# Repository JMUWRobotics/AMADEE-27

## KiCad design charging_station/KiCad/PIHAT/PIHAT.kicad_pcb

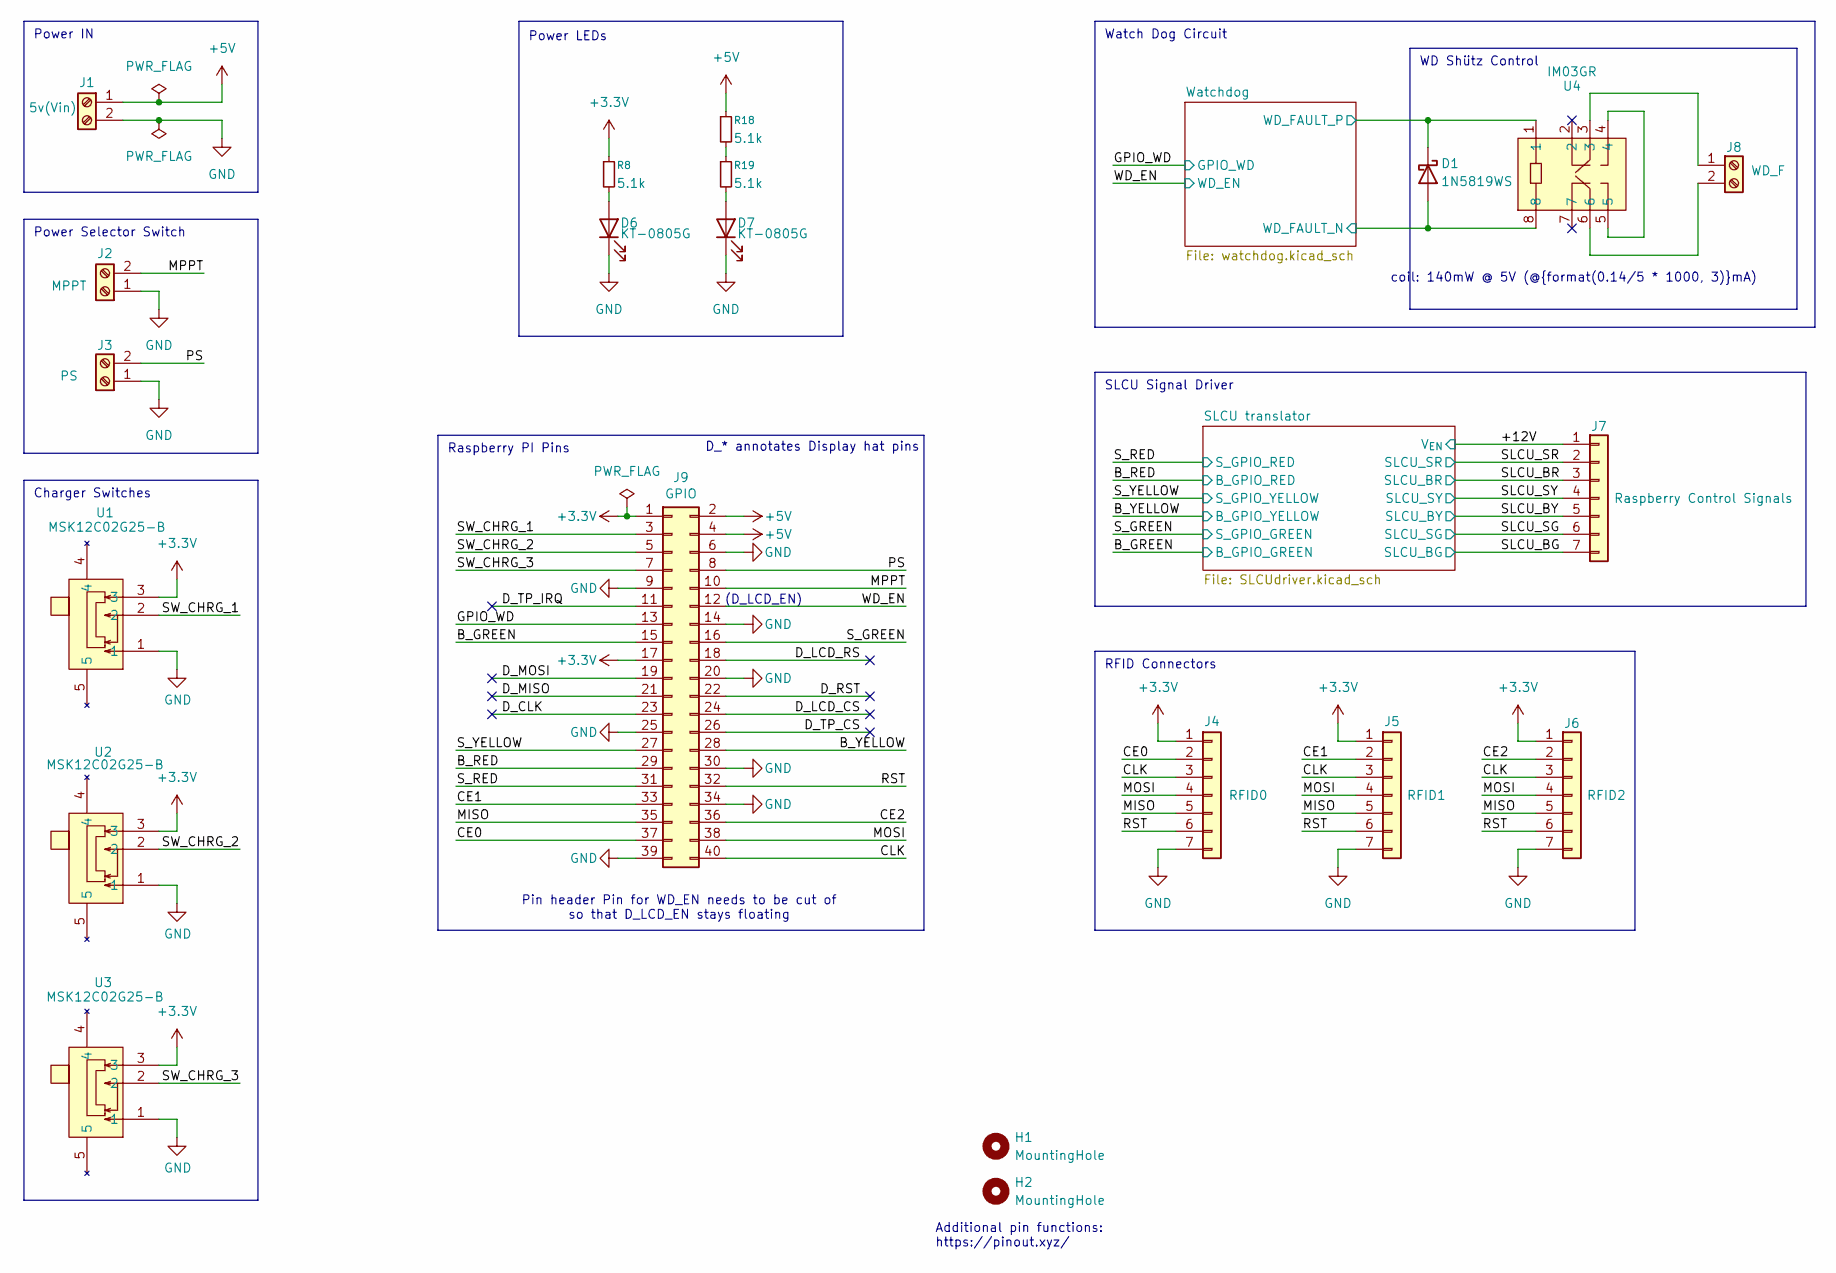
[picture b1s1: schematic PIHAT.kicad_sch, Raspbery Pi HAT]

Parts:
D1: 1N5819WS; D_SOD-323; LCSC C191023
D6, D7: KT-0805G; LED_0805_2012Metric; MPN KT-0805G; LCSC Part C2297
H1: MountingHole; MountingHole_2.2mm_M2_DIN965_Pad
H2: MountingHole; MountingHole_2.5mm_Pad
J1: 5v(Vin); TerminalBlock_Phoenix_PT-1,5-2-5.0-H_1x02_P5.00mm_Horizontal; MPN 1935161; LCSC Part C3819953
J2: MPPT; TerminalBlock_Phoenix_PT-1,5-2-5.0-H_1x02_P5.00mm_Horizontal; MPN 1935161; LCSC Part C3819953
J3: PS; TerminalBlock_Phoenix_PT-1,5-2-5.0-H_1x02_P5.00mm_Horizontal; MPN 1935161; LCSC Part C3819953
J4: RFID0; JST_XH_S7B-XH-A_1x07_P2.50mm_Horizontal; MPN S7B-XH-A(LF)(SN); LCSC Part C157916
J5: RFID1; JST_XH_S7B-XH-A_1x07_P2.50mm_Horizontal; MPN S7B-XH-A(LF)(SN); LCSC Part C157916
J6: RFID2; JST_XH_S7B-XH-A_1x07_P2.50mm_Horizontal; MPN S7B-XH-A(LF)(SN); LCSC Part C157916
J7: Raspberry Control Signals; JST_XH_S7B-XH-A_1x07_P2.50mm_Horizontal; MPN S7B-XH-A(LF)(SN); LCSC Part C157916
J8: WD_F; TerminalBlock_Phoenix_PT-1,5-2-5.0-H_1x02_P5.00mm_Horizontal; MPN 1935161; LCSC Part C3819953
J9: GPIO; PinSocket_2x20_P2.54mm_Vertical; MPN SSQ-120-03-T-D; LCSC C6235776
R8, R18, R19: 5.1k; R_0603_1608Metric; LCSC C17414
U1, U2, U3: MSK12C02G25-B; SW-SMD_MSK12C02G25-B; MPN MSK12C02G25-B; LCSC Part C22435663
U4: IM03GR; RELAY-SMD_IMXXGR; MPN IM03GR; LCSC Part C2153100

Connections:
+3.3V: J4.1, J5.1, J6.1, J9.1, J9.17, R8.1, U1.3, U2.3, U3.3; also elsewhere on the board
+5V: J1.1, J9.2, J9.4, R18.1; also elsewhere on the board
/+12V: J7.1; also elsewhere on the board
/B_GREEN: J9.15; also elsewhere on the board
/B_RED: J9.29; also elsewhere on the board
/B_YELLOW: J9.28; also elsewhere on the board
/CE0: J4.2, J9.37
/CE1: J5.2, J9.33
/CE2: J6.2, J9.36
/CLK: J4.3, J5.3, J6.3, J9.40
/D_CLK: J9.23
/D_LCD_CS: J9.24
/D_LCD_RS: J9.18
/D_MISO: J9.21
/D_MOSI: J9.19
/D_RST: J9.22
/D_TP_CS: J9.26
/D_TP_IRQ: J9.11
/GPIO_WD: J9.13; also elsewhere on the board
/MISO: J4.5, J5.5, J6.5, J9.35
/MOSI: J4.4, J5.4, J6.4, J9.38
/MPPT: J2.2, J9.10
/PS: J3.2, J9.8
/RST: J4.6, J5.6, J6.6, J9.32
/SLCU_BG: J7.7; also elsewhere on the board
/SLCU_BR: J7.3; also elsewhere on the board
/SLCU_BY: J7.5; also elsewhere on the board
/SLCU_SG: J7.6; also elsewhere on the board
/SLCU_SR: J7.2; also elsewhere on the board
/SLCU_SY: J7.4; also elsewhere on the board
/SW_CHRG_1: J9.3, U1.2
/SW_CHRG_2: J9.5, U2.2
/SW_CHRG_3: J9.7, U3.2
/S_GREEN: J9.16; also elsewhere on the board
/S_RED: J9.31; also elsewhere on the board
/S_YELLOW: J9.27; also elsewhere on the board
/WD_EN: J9.12; also elsewhere on the board
/Watchdog/WD_FAULT_N: D1.2 (A), U4.8; also elsewhere on the board
/Watchdog/WD_FAULT_P: D1.1 (K), U4.1; also elsewhere on the board
GND: D6.1 (K), D7.1 (K), J1.2, J2.1, J3.1, J4.7, J5.7, J6.7, J9.6, J9.9, J9.14, J9.20, J9.25, J9.30, J9.34, J9.39, U1.1, U2.1, U3.1; also elsewhere on the board
unnamed: D6.2 (A), R8.2
unnamed: D7.2 (A), R19.2
unnamed: J8.1, U4.3
unnamed: J8.2, U4.6
unnamed: R18.2, R19.1
unnamed: U4.4, U4.5

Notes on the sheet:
Raspberry PI Pins
(D_LCD_EN)
Additional pin functions: https://pinout.xyz/
SLCU Signal Driver
RFID Connectors
WD Shütz Control
Pin header Pin for WD_EN needs to be cut of so that D_LCD_EN stays floating
Power Selector Switch
Watch Dog Circuit
Power LEDs
Charger Switches
Power IN
coil: 140mW @ 5V (@{format(0.14/5 * 1000, 3)}mA)
D_* annotates Display hat pins

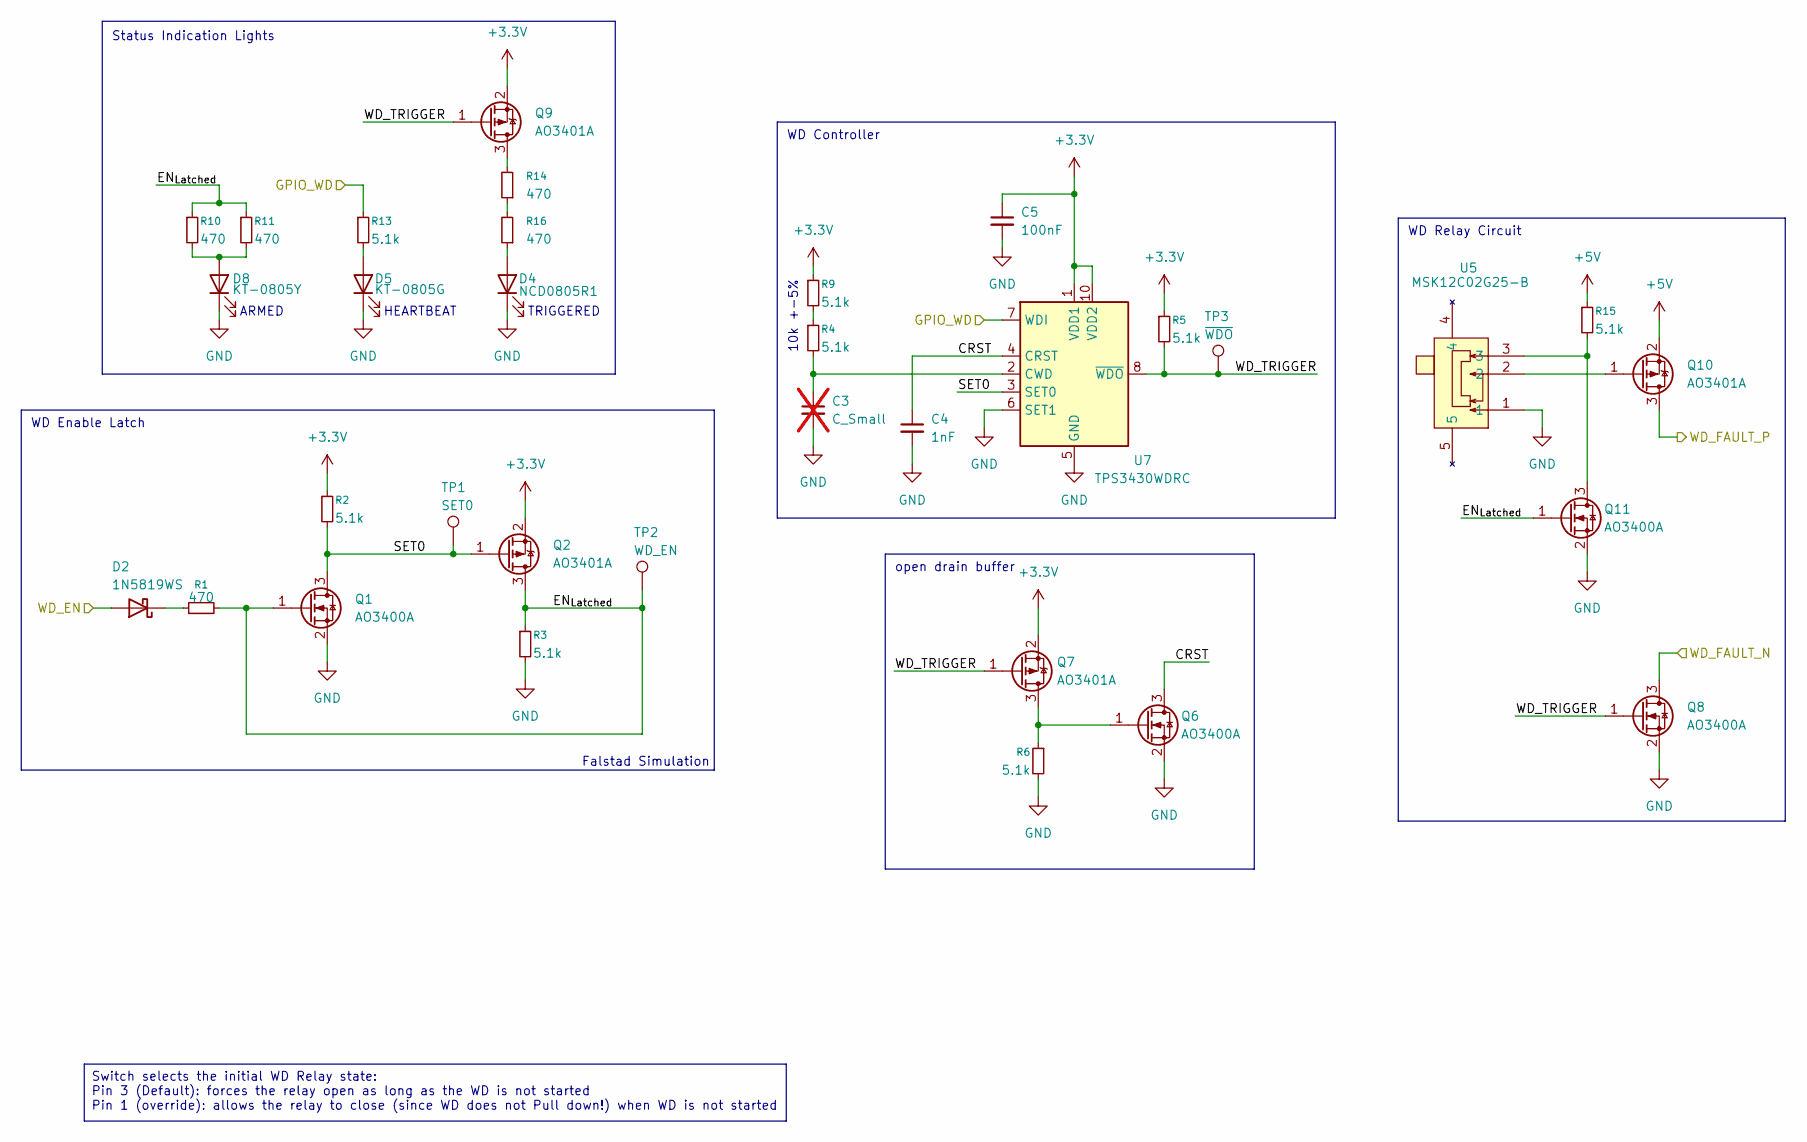
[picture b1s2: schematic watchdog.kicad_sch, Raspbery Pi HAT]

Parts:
C3: C_Small; C_0805_2012Metric_Pad1.18x1.45mm_HandSolder; not fitted
C4: 1nF; C_0603_1608Metric
C5: 100nF; C_0603_1608Metric; LCSC Part C14663
D2: 1N5819WS; D_SOD-323; LCSC C191023
D4: NCD0805R1; LED_0805_2012Metric; MPN NCD0805R1; LCSC Part C84256
D5: KT-0805G; LED_0805_2012Metric; MPN KT-0805G; LCSC Part C2297
D8: KT-0805Y; LED_0805_2012Metric; MPN KT-0805Y; LCSC Part C2296
Q1, Q6, Q8, Q11: AO3400A; SOT-23; MPN AO3400A; LCSC Part C15127
Q2, Q7, Q9, Q10: AO3401A; SOT-23; MPN AO3401A; LCSC Part C15127
R1, R10, R11, R14, R16: 470; R_0603_1608Metric; LCSC C23179
R2, R3, R4, R5, R6, R9, R13, R15: 5.1k; R_0603_1608Metric; LCSC C17414
TP1: SET0; TestPoint_Pad_D1.0mm
TP2: WD_EN; TestPoint_Pad_D1.0mm
TP3: ~{WDO}; TestPoint_Pad_D1.0mm
U5: MSK12C02G25-B; SW-SMD_MSK12C02G25-B; MPN MSK12C02G25-B; LCSC Part C22435663
U7: TPS3430WDRC; VSON-10-1EP_3x3mm_P0.5mm_EP1.65x2.4mm

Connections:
+3.3V: C5.1, Q2.2 (S), Q7.2 (S), Q9.2 (S), R2.1, R5.1, R9.1, U7.1 (VDD1), U7.10 (VDD2); also elsewhere on the board
+5V: Q10.2 (S), R15.1; also elsewhere on the board
/GPIO_WD: R13.1, U7.7 (WDI); also elsewhere on the board
/WD_EN: D2.2 (A); also elsewhere on the board
/Watchdog/CRST: C4.1, Q6.3 (D), U7.4 (CRST)
/Watchdog/EN_{Latched}: Q1.1 (G), Q2.3 (D), Q11.1 (G), R1.2, R3.1, R10.1, R11.1, TP2.1 (1_1)
/Watchdog/SET0: Q1.3 (D), Q2.1 (G), R2.2, TP1.1 (1_1), U7.3 (SET0)
/Watchdog/WD_FAULT_N: Q8.3 (D); also elsewhere on the board
/Watchdog/WD_FAULT_P: Q10.3 (D); also elsewhere on the board
/Watchdog/WD_TRIGGER: Q7.1 (G), Q8.1 (G), Q9.1 (G), R5.2, TP3.1 (1_1), U7.8 (~WDO)
GND: C3.2, C4.2, C5.2, D4.1 (K), D5.1 (K), D8.1 (K), Q1.2 (S), Q6.2 (S), Q8.2 (S), Q11.2 (S), R3.2, R6.2, U5.1, U7.5 (GND), U7.6 (SET1), U7.11 (GND); also elsewhere on the board
unnamed: D2.1 (K), R1.1
unnamed: D4.2 (A), R16.1
unnamed: D5.2 (A), R13.2
unnamed: D8.2 (A), R10.2, R11.2
unnamed: Q6.1 (G), Q7.3 (D), R6.1
unnamed: Q9.3 (D), R14.2
unnamed: Q10.1 (G), U5.2
unnamed: Q11.3 (D), R15.2, U5.3
unnamed: R4.1, R9.2
unnamed: R14.1, R16.2
unnamed: C3.1, R4.2, U7.2 (CWD)

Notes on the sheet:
HEARTBEAT
open drain buffer
10k +-5%
Falstad Simulation
WD Enable Latch
TRIGGERED
Status Indication Lights
ARMED
WD Controller
WD Relay Circuit
Switch selects the initial WD Relay state: Pin 3 (Default): forces the relay open as long as the WD is not started Pin 1 (override): allows the relay to close (since WD does not Pull down!) when WD is not started

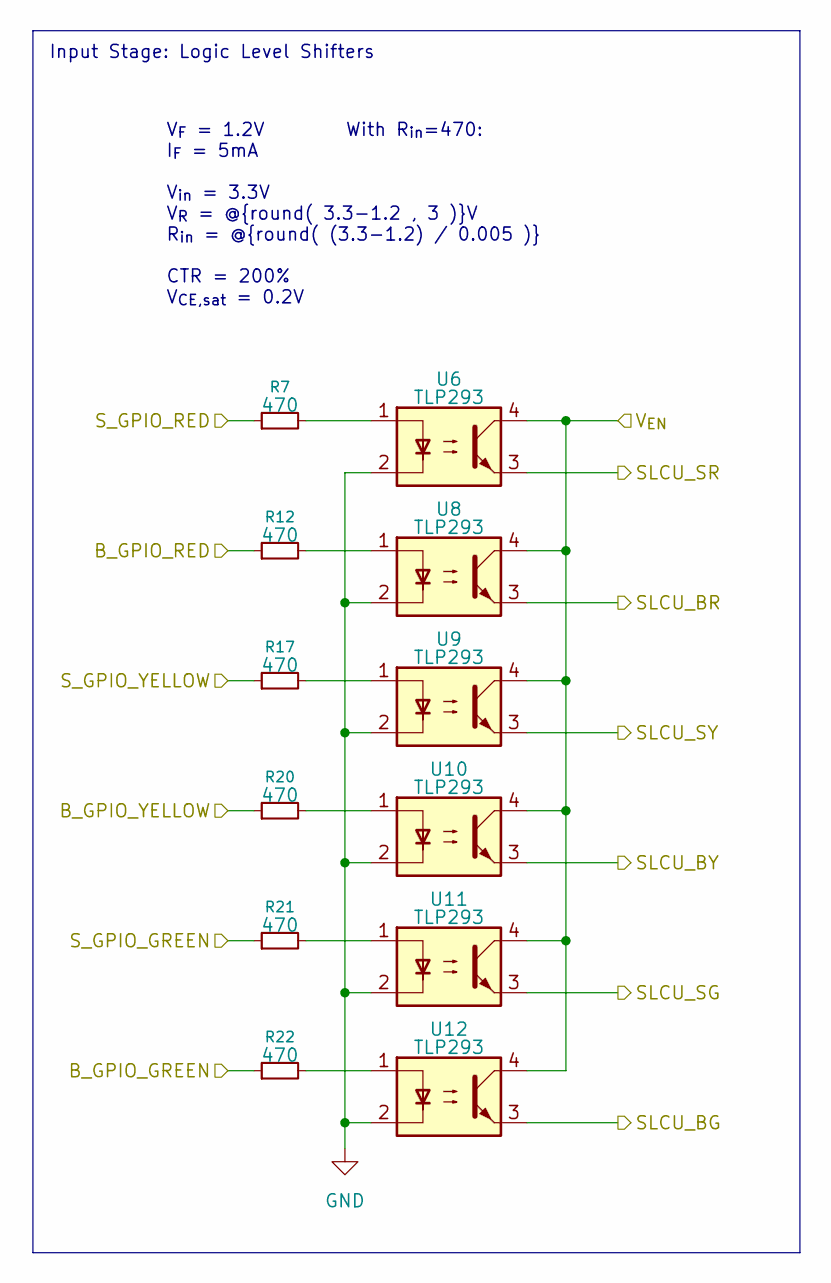
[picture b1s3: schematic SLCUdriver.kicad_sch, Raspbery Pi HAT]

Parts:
R7, R12, R17, R20, R21, R22: 470; R_0603_1608Metric; LCSC C23179
U6, U8, U9, U10, U11, U12: TLP293; SOIC-4_4.55x2.6mm_P1.27mm; MPN TLP293(BLL-TPL,E; LCSC C3008594

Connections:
/+12V: U6.4, U8.4, U9.4, U10.4, U11.4, U12.4; also elsewhere on the board
/B_GREEN: R22.1; also elsewhere on the board
/B_RED: R12.1; also elsewhere on the board
/B_YELLOW: R20.1; also elsewhere on the board
/SLCU_BG: U12.3; also elsewhere on the board
/SLCU_BR: U8.3; also elsewhere on the board
/SLCU_BY: U10.3; also elsewhere on the board
/SLCU_SG: U11.3; also elsewhere on the board
/SLCU_SR: U6.3; also elsewhere on the board
/SLCU_SY: U9.3; also elsewhere on the board
/S_GREEN: R21.1; also elsewhere on the board
/S_RED: R7.1; also elsewhere on the board
/S_YELLOW: R17.1; also elsewhere on the board
GND: U6.2, U8.2, U9.2, U10.2, U11.2, U12.2; also elsewhere on the board
unnamed: R7.2, U6.1
unnamed: R12.2, U8.1
unnamed: R17.2, U9.1
unnamed: R20.2, U10.1
unnamed: R21.2, U11.1
unnamed: R22.2, U12.1

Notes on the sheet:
With R_{in}=470:
V_{F} = 1.2V I_{F} = 5mA V_{in} = 3.3V V_{R} = @{round( 3.3-1.2 , 3 )}V R_{in} = @{round( (3.3-1.2) / 0.005 )} CTR = 200% V_{CE,sat} = 0.2V
Input Stage: Logic Level Shifters

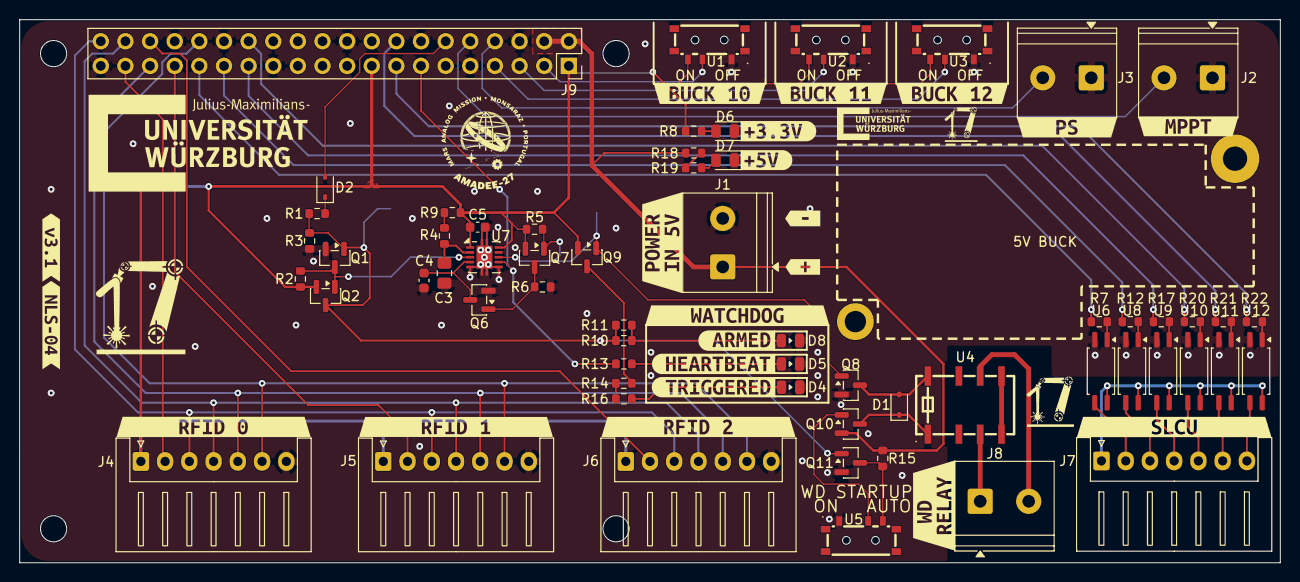
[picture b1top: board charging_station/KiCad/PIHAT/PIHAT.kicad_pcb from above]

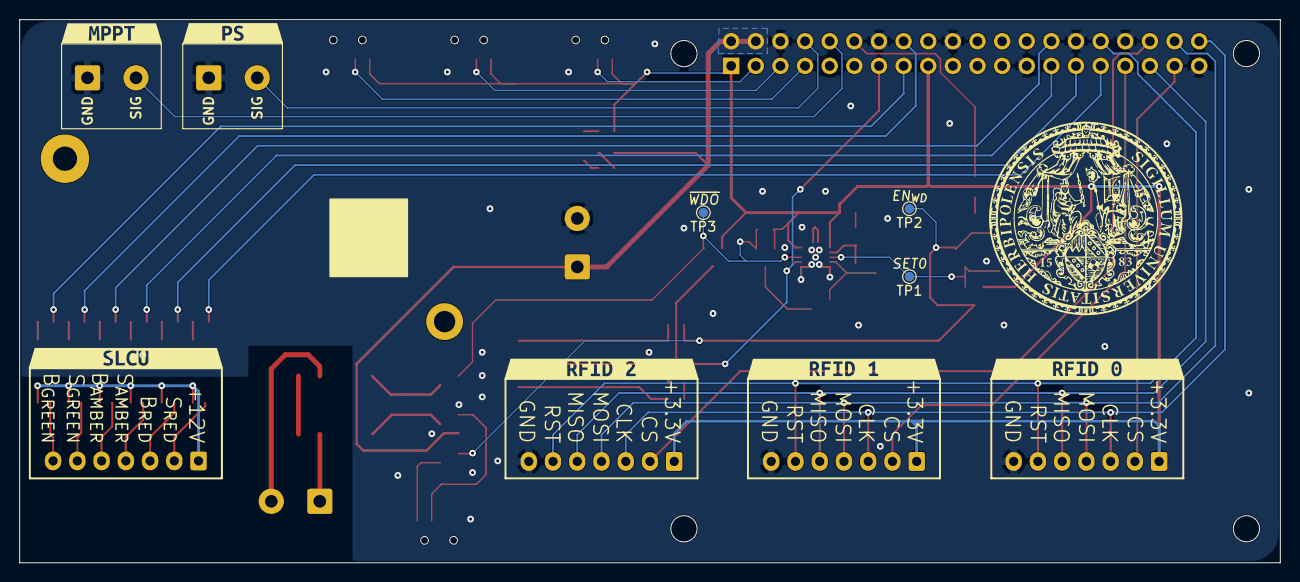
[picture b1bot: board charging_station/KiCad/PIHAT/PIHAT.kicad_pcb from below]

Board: 2 copper layers, 130.0 x 56.0 mm, 97 parts (13 on the bottom side), 59 nets.

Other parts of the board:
MH1, MH2, MH3, MH4: MountingHole_2.7mm_M2.5
kibuzzard-6AD53C3D: G***; kibuzzard-6AD53C3D
kibuzzard-6AD53C20, kibuzzard-6AD53C20#2: G***; kibuzzard-6AD53C20
kibuzzard-6AD53C43: G***; kibuzzard-6AD53C43
kibuzzard-6AD53C84: G***; kibuzzard-6AD53C84
kibuzzard-6AD53CF1: G***; kibuzzard-6AD53CF1
kibuzzard-6AD53D49: G***; kibuzzard-6AD53D49
kibuzzard-6AD53DF3: G***; kibuzzard-6AD53DF3
kibuzzard-6AD53E3A: G***; kibuzzard-6AD53E3A
kibuzzard-6AD53E40: G***; kibuzzard-6AD53E40
kibuzzard-6AD530C8: G***; kibuzzard-6AD530C8
kibuzzard-6AD530EA: G***; kibuzzard-6AD530EA
kibuzzard-6AD537E7: G***; kibuzzard-6AD537E7
kibuzzard-6AD540AE: G***; kibuzzard-6AD540AE
kibuzzard-6AD541D1: G***; kibuzzard-6AD541D1
kibuzzard-6AD543B1: G***; kibuzzard-6AD543B1
kibuzzard-6AD543B7: G***; kibuzzard-6AD543B7
kibuzzard-6AD554A5: G***; kibuzzard-6AD554A5
kibuzzard-6AD5310E: G***; kibuzzard-6AD5310E
kibuzzard-6AD5403C: G***; kibuzzard-6AD5403C
kibuzzard-6AD54089: G***; kibuzzard-6AD54089
kibuzzard-6AF5E61E: G***; kibuzzard-6AF5E61E
kibuzzard-6AF5E623: G***; kibuzzard-6AF5E623
kibuzzard-6AF5EA3F: G***; kibuzzard-6AF5EA3F
kibuzzard-6AF5F1CD: G***; kibuzzard-6AF5F1CD
kibuzzard-6AF5F1D2: G***; kibuzzard-6AF5F1D2
kibuzzard-6AF35593: G***; kibuzzard-6AF35593

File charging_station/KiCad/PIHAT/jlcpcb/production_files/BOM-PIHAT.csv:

Comment,Designator,Footprint,LCSC,Quantity
100nF,C5,C_0603_1608Metric,C14663,1
1N5819WS,"D1,D2",D_SOD-323,C191023,2
1nF,C4,C_0603_1608Metric,C1588,1
470,"R1,R10,R11,R12,R14,R16,R17,R20,R21,R22,R7",R_0603_1608Metric,C23179,11
5.1k,"R13,R15,R18,R19,R2,R3,R4,R5,R6,R8,R9",R_0603_1608Metric,C23186,11
5v(Vin),J1,"TerminalBlock_Phoenix_PT-1,5-2-5.0-H_1x02_P5.00mm_Horizontal",C3819953,1
AO3400A,"Q1,Q11,Q6,Q8",SOT-23,C20917,4
AO3401A,"Q10,Q2,Q7,Q9",SOT-23,C15127,4
GPIO,J9,PinSocket_2x20_P2.54mm_Vertical,C6235776,1
IM03GR,U4,RELAY-SMD_IMXXGR,C2153100,1
KT-0805G,"D5,D6,D7",LED_0805_2012Metric,C2297,3
KT-0805Y,D8,LED_0805_2012Metric,C2296,1
MPPT,J2,"TerminalBlock_Phoenix_PT-1,5-2-5.0-H_1x02_P5.00mm_Horizontal",C3819953,1
MSK12C02G25-B,"U1,U2,U3,U5",SW-SMD_MSK12C02G25-B,C22435663,4
NCD0805R1,D4,LED_0805_2012Metric,C84256,1
PS,J3,"TerminalBlock_Phoenix_PT-1,5-2-5.0-H_1x02_P5.00mm_Horizontal",C3819953,1
RFID0,J4,JST_XH_S7B-XH-A_1x07_P2.50mm_Horizontal,C157916,1
RFID1,J5,JST_XH_S7B-XH-A_1x07_P2.50mm_Horizontal,C157916,1
RFID2,J6,JST_XH_S7B-XH-A_1x07_P2.50mm_Horizontal,C157916,1
Raspberry Control Signals,J7,JST_XH_S7B-XH-A_1x07_P2.50mm_Horizontal,C157916,1
TLP293,"U10,U11,U12,U6,U8,U9",SOIC-4_4.55x2.6mm_P1.27mm,C3008594,6
TPS3430WDRC,U7,VSON-10-1EP_3x3mm_P0.5mm_EP1.65x2.4mm,C2870545,1
WD_F,J8,"TerminalBlock_Phoenix_PT-1,5-2-5.0-H_1x02_P5.00mm_Horizontal",C3819953,1

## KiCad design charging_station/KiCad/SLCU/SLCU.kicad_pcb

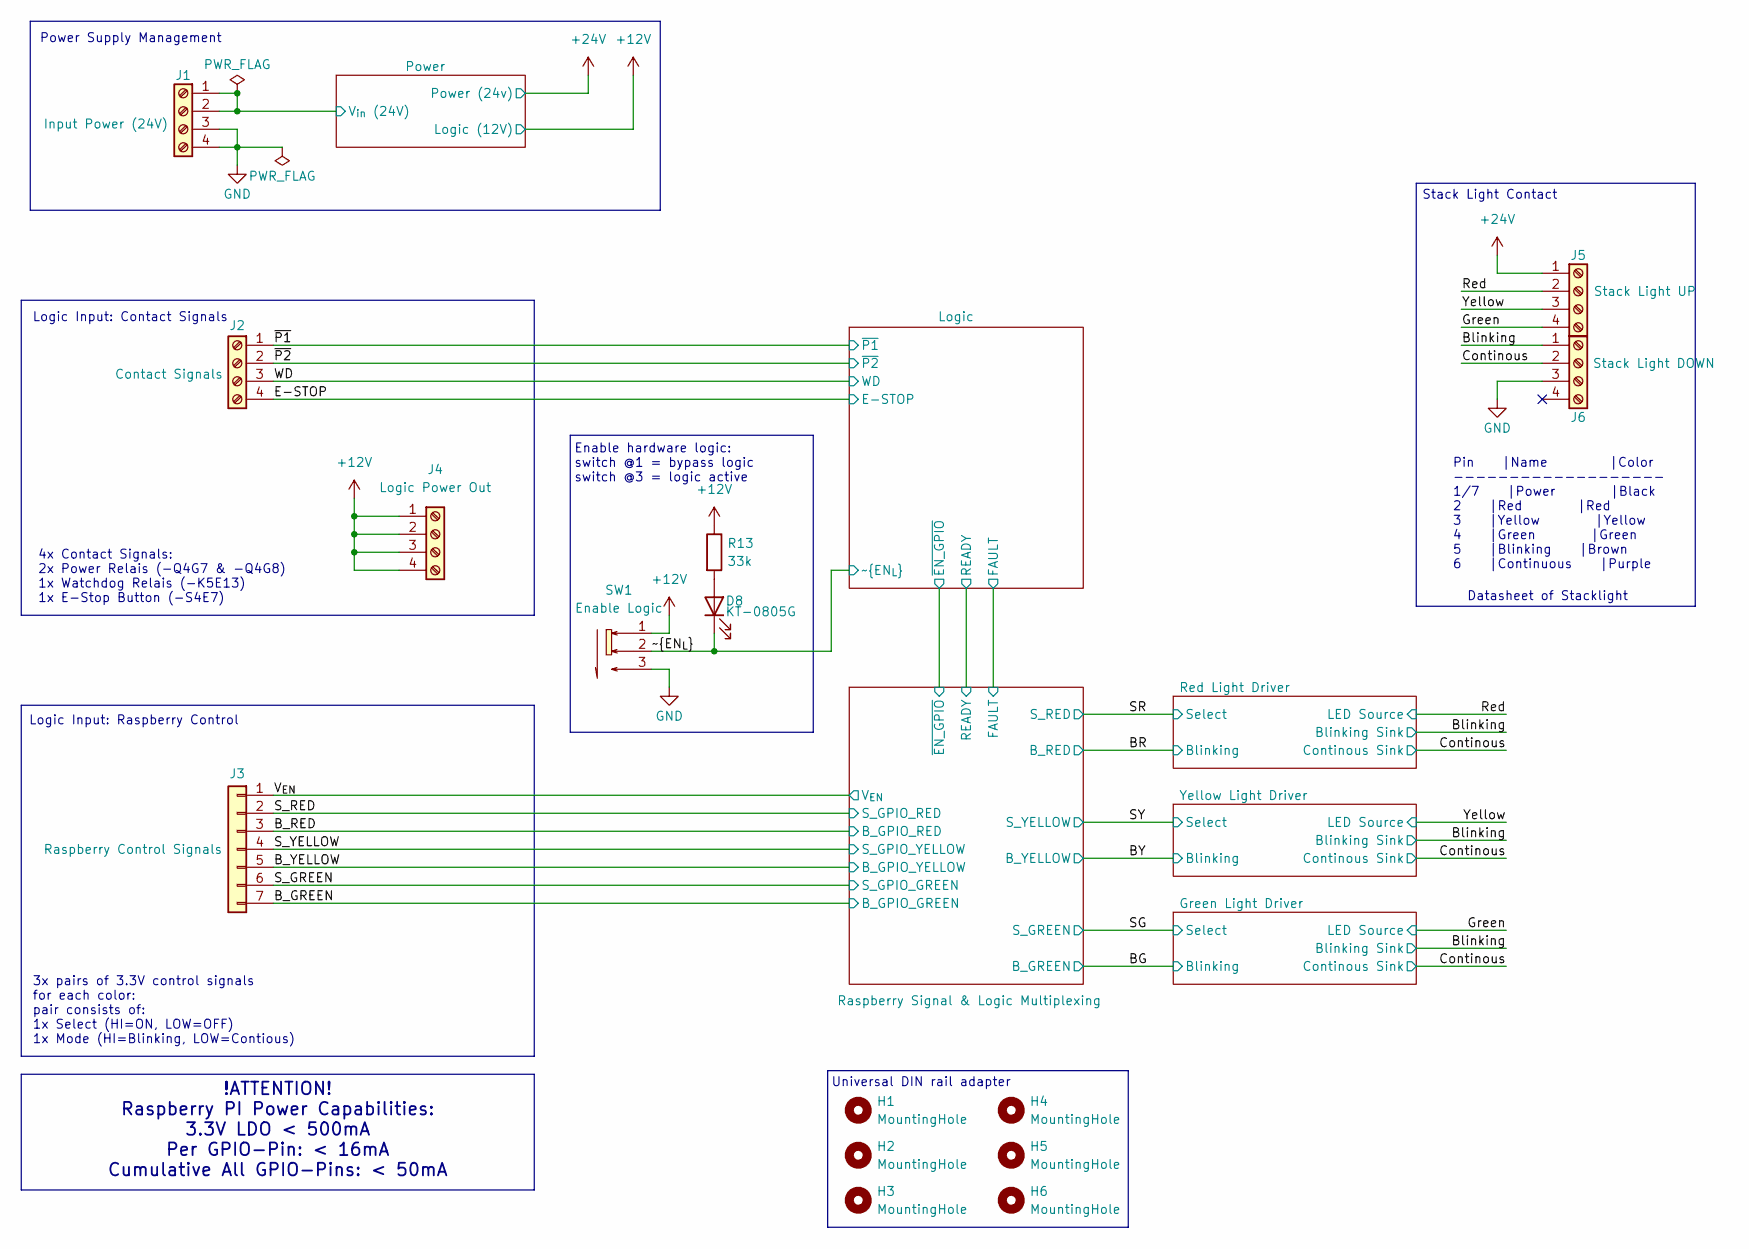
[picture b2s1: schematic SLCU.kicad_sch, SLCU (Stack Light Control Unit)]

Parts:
D8: KT-0805G; LED_0805_2012Metric_Pad1.15x1.40mm_HandSolder; MPN KT-0805G; LCSC Part C2297
H1, H2, H3, H4, H5, H6: MountingHole; MountingHole_3.2mm_M3
J1: Input Power (24V); TerminalBlock_Phoenix_MKDS-1,5-4_1x04_P5.00mm_Horizontal; MPN 1935187; LCSC Part C3817931
J2: Contact Signals; TerminalBlock_Phoenix_MKDS-1,5-4_1x04_P5.00mm_Horizontal; MPN 1935187; LCSC Part C3817931
J3: Raspberry Control Signals; JST_XH_S7B-XH-A_1x07_P2.50mm_Horizontal; MPN S7B-XH-A(LF)(SN); LCSC Part C157916
J4: Logic Power Out; TerminalBlock_Phoenix_MKDS-1,5-4_1x04_P5.00mm_Horizontal; MPN 1935187; LCSC Part C3817931
J5: Stack Light UP; TerminalBlock_Phoenix_MKDS-1,5-4_1x04_P5.00mm_Horizontal; MPN 1935187; LCSC Part C3817931
J6: Stack Light DOWN; TerminalBlock_Phoenix_MKDS-1,5-4_1x04_P5.00mm_Horizontal; MPN 1935187; LCSC Part C3817931
R13: 33k; R_0402_1005Metric; LCSC Part C25779
SW1: Enable Logic; SW-SMD_SHOUHAN_MST-22D18G23J_C2875122; MPN MST-22D18G2 3J; LCSC Part C2875122

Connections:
+12V: J4.1, J4.2, J4.3, J4.4, R13.1, SW1.1; also elsewhere on the board
+24V: J5.1; also elsewhere on the board
/B_GREEN: J3.7; also elsewhere on the board
/B_RED: J3.3; also elsewhere on the board
/B_YELLOW: J3.5; also elsewhere on the board
/Blinking: J6.1; also elsewhere on the board
/Continous: J6.2; also elsewhere on the board
/E-STOP: J2.4; also elsewhere on the board
/Green: J5.4; also elsewhere on the board
/Power/V_{in} (24V): J1.1, J1.2; also elsewhere on the board
/Red: J5.2; also elsewhere on the board
/S_GREEN: J3.6; also elsewhere on the board
/S_RED: J3.2; also elsewhere on the board
/S_YELLOW: J3.4; also elsewhere on the board
/V_{EN}: J3.1; also elsewhere on the board
/WD: J2.3; also elsewhere on the board
/Yellow: J5.3; also elsewhere on the board
/~EN_{L}: D8.1 (K), SW1.2; also elsewhere on the board
/~P1: J2.1; also elsewhere on the board
/~P2: J2.2; also elsewhere on the board
GND: J1.3, J1.4, J6.3, SW1.3; also elsewhere on the board
unnamed: D8.2 (A), R13.2

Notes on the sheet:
Enable hardware logic: switch @1 = bypass logic switch @3 = logic active
Logic Input: Raspberry Control
Power Supply Management
Datasheet of Stacklight
Pin |Name |Color ------------------- 1/7 |Power |Black 2 |Red |Red 3 |Yellow |Yellow 4 |Green |Green 5 |Blinking |Brown 6 |Continuous |Purple
Logic Input: Contact Signals
3x pairs of 3.3V control signals for each color: pair consists of: 1x Select (HI=ON, LOW=OFF) 1x Mode (HI=Blinking, LOW=Contious)
Stack Light Contact
Universal DIN rail adapter
4x Contact Signals: 2x Power Relais (-Q4G7 & -Q4G8) 1x Watchdog Relais (-K5E13) 1x E-Stop Button (-S4E7)
!ATTENTION! Raspberry PI Power Capabilities: 3.3V LDO < 500mA Per GPIO-Pin: < 16mA Cumulative All GPIO-Pins: < 50mA

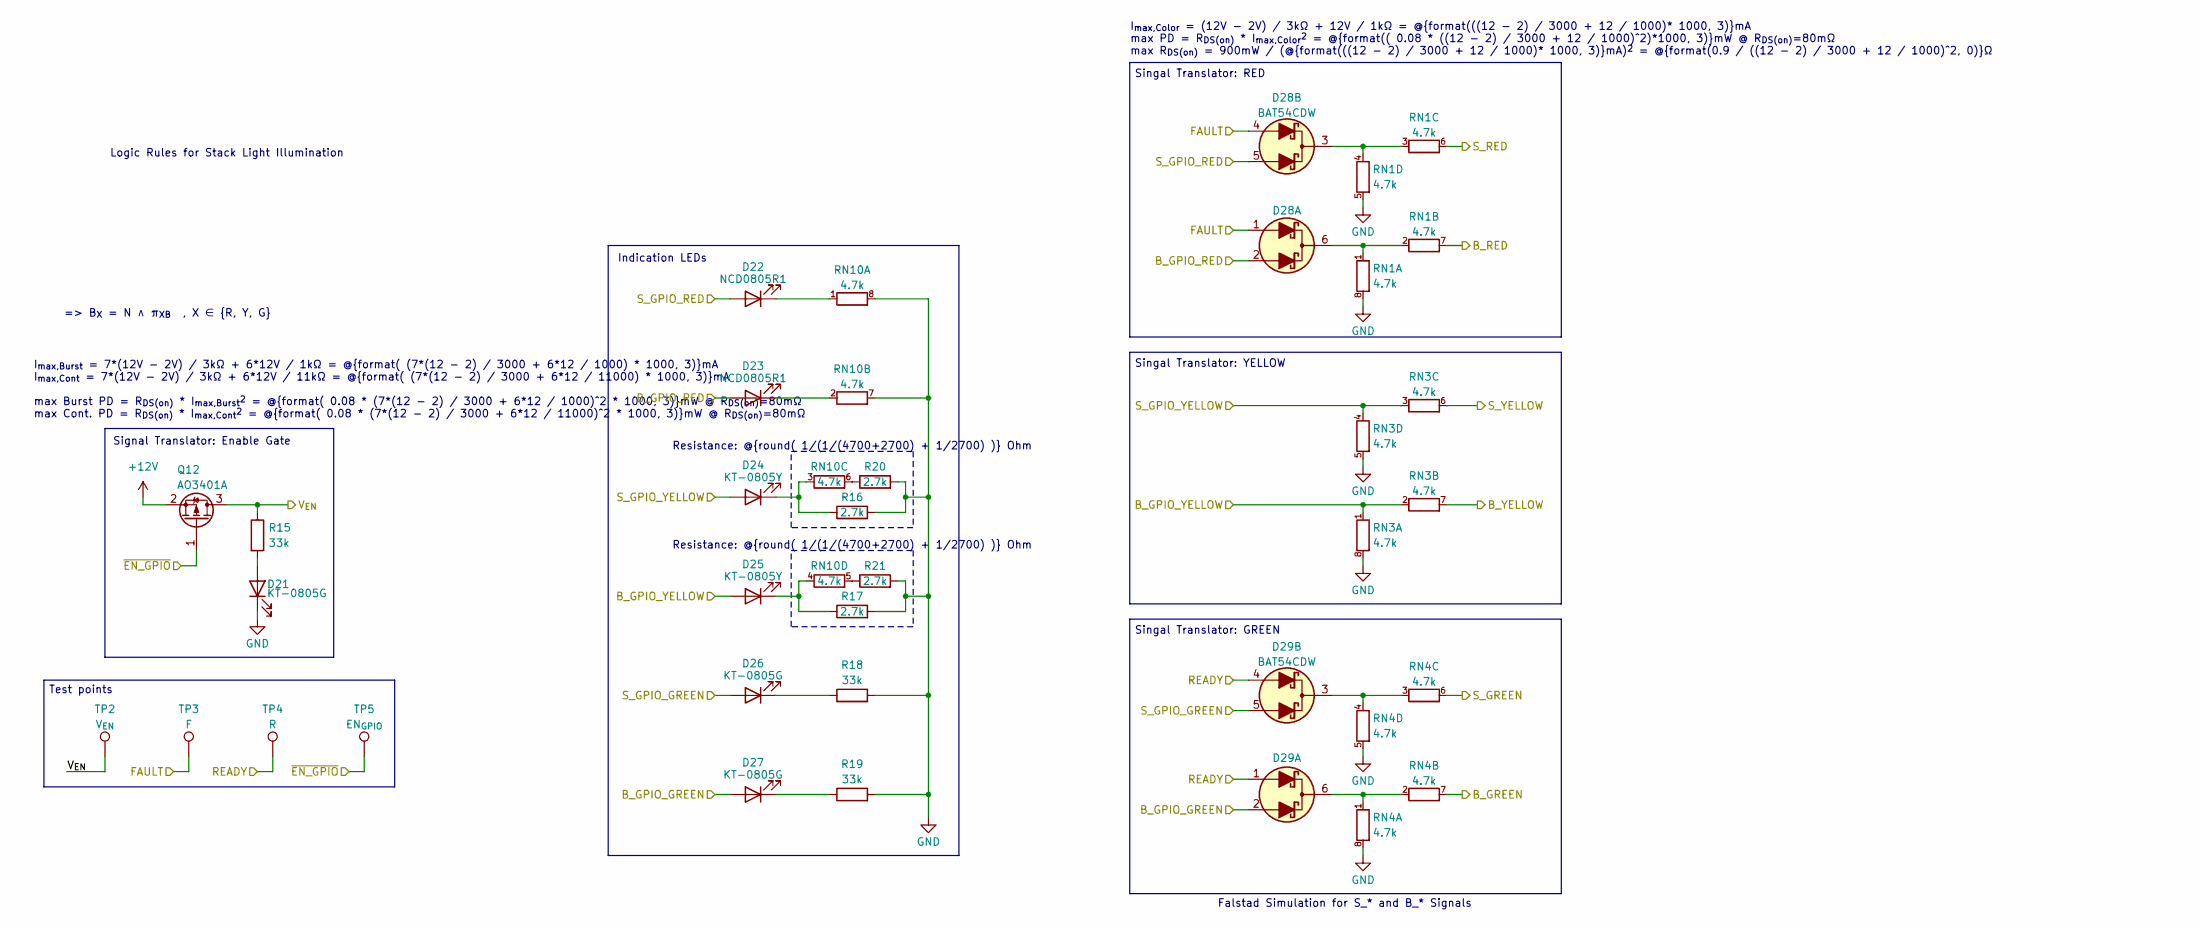
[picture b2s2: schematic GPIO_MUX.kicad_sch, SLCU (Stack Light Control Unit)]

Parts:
D21, D26, D27: KT-0805G; LED_0805_2012Metric_Pad1.15x1.40mm_HandSolder; MPN KT-0805G; LCSC Part C2297
D22, D23: NCD0805R1; LED_0805_2012Metric_Pad1.15x1.40mm_HandSolder; MPN NCD0805R1; LCSC Part C84256
D24, D25: KT-0805Y; LED_0805_2012Metric_Pad1.15x1.40mm_HandSolder; MPN KT-0805Y; LCSC Part C2296
D28, D29: BAT54CDW; SOT-363_SC-70-6
Q12: AO3401A; SOT-23; MPN AO3401A; LCSC Part C15127
R15, R18, R19: 33k; R_0402_1005Metric; LCSC Part C25779
R16, R17, R20, R21: 2.7k; R_0603_1608Metric; LCSC Part C13167
RN1, RN3, RN4, RN10: 4.7k; RES-ARRAY-SMD_0603-8P-L3.2-W1.6-BL; MPN 4D03WGJ0472T5E; LCSC Part C1980
TP2: V_{EN}; TestPoint_Pad_D1.0mm
TP3: F; TestPoint_Pad_D1.0mm
TP4: R; TestPoint_Pad_D1.0mm
TP5: EN_{GPIO}; TestPoint_Pad_D1.0mm

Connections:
+12V: Q12.2 (S); also elsewhere on the board
/BG: RN4.7 (R2.2); also elsewhere on the board
/BR: RN1.7 (R2.2); also elsewhere on the board
/BY: RN3.7 (R2.2); also elsewhere on the board
/B_GREEN: D27.2 (A), D29.2 (A1); also elsewhere on the board
/B_RED: D23.2 (A), D28.2 (A1); also elsewhere on the board
/B_YELLOW: D25.2 (A), RN3.1 (R1.1), RN3.2 (R2.1); also elsewhere on the board
/Logic/FAULT: D28.1 (A1), D28.4 (A2), TP3.1 (1_1); also elsewhere on the board
/Logic/READY: D29.1 (A1), D29.4 (A2), TP4.1 (1_1); also elsewhere on the board
/Logic/~EN_GPIO: Q12.1 (G), TP5.1 (1_1); also elsewhere on the board
/SG: RN4.6 (R3.2); also elsewhere on the board
/SR: RN1.6 (R3.2); also elsewhere on the board
/SY: RN3.6 (R3.2); also elsewhere on the board
/S_GREEN: D26.2 (A), D29.5 (A2); also elsewhere on the board
/S_RED: D22.2 (A), D28.5 (A2); also elsewhere on the board
/S_YELLOW: D24.2 (A), RN3.3 (R3.1), RN3.4 (R4.1); also elsewhere on the board
/V_{EN}: Q12.3 (D), R15.1, TP2.1 (1_1); also elsewhere on the board
GND: D21.1 (K), R16.2, R17.2, R18.2, R19.2, R20.2, R21.2, RN1.5 (R4.2), RN1.8 (R1.2), RN3.5 (R4.2), RN3.8 (R1.2), RN4.5 (R4.2), RN4.8 (R1.2), RN10.7 (R2.2), RN10.8 (R1.2); also elsewhere on the board
unnamed: D21.2 (A), R15.2
unnamed: D22.1 (K), RN10.1 (R1.1)
unnamed: D23.1 (K), RN10.2 (R2.1)
unnamed: D24.1 (K), R16.1, RN10.3 (R3.1)
unnamed: D25.1 (K), R17.1, RN10.4 (R4.1)
unnamed: D26.1 (K), R18.1
unnamed: D27.1 (K), R19.1
unnamed: D28.6 (K1), RN1.1 (R1.1), RN1.2 (R2.1)
unnamed: D28.3 (K2), RN1.3 (R3.1), RN1.4 (R4.1)
unnamed: D29.6 (K1), RN4.1 (R1.1), RN4.2 (R2.1)
unnamed: D29.3 (K2), RN4.3 (R3.1), RN4.4 (R4.1)
unnamed: R20.1, RN10.6 (R3.2)
unnamed: R21.1, RN10.5 (R4.2)

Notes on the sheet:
Singal Translator: GREEN
I_{max,Burst} = 7*(12V - 2V) / 3kΩ + 6*12V / 1kΩ = @{format( (7*(12 - 2) / 3000 + 6*12 / 1000) * 1000, 3)}mA I_{max,Cont} = 7*(12V - 2V) / 3kΩ + 6*12V / 11kΩ = @{format( (7*(12 - 2) / 3000 + 6*12 / 11000) * 1000, 3)}mA max Burst PD = R_{DS(on)} * I_{max,Burst}^{2} = @{format( 0.08 * (7*(12 - 2) / 3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
Falstad Simulation for S_* and B_* Signals
Signal Translator: Enable Gate
Resistance: @{round( 1/(1/(4700+2700) + 1/2700) )} Ohm
Singal Translator: YELLOW
Indication LEDs
=> B_{X} = N ∧ π_{XB} , X ∈ {R, Y, G}
Test points
I_{max,Color} = (12V - 2V) / 3kΩ + 12V / 1kΩ = @{format(((12 - 2) / 3000 + 12 / 1000)* 1000, 3)}mA max PD = R_{DS(on)} * I_{max,Color}^{2} = @{format(( 0.08 * ((12 - 2) / 3000 + 12 / 1000)^2)*1000, 3)}mW @ R_{DS(on)}=80mΩ max R_{DS(on)} = 900mW / (@{format(((12 - 2) / 3000 + 12 / 1000)* 1000, 3)}mA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
Singal Translator: RED
Logic Rules for Stack Light Illumination

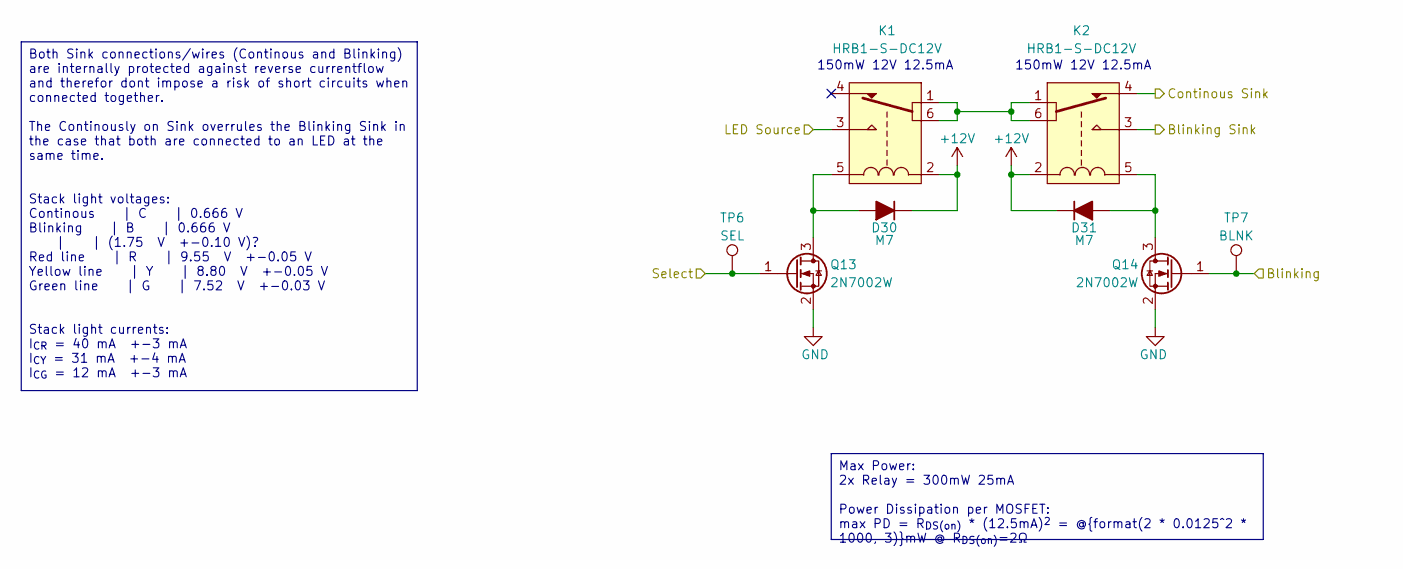
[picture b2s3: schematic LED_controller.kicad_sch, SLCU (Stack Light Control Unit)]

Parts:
D30, D31: M7; D_SMA
K1, K2: HRB1-S-DC12V; RELAY-TH_HRB1-S-X; MPN HRB1-S-DC12V; LCSC Part C125705
Q13, Q14: 2N7002W; SOT-323_SC-70; MPN 2N7002W; LCSC Part C7420322
TP6: SEL; TestPoint_Pad_D1.0mm
TP7: BLNK; TestPoint_Pad_D1.0mm

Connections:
+12V: D30.1 (K), D31.1 (K), K1.2, K2.2; also elsewhere on the board
/BR: Q14.1 (G), TP7.1 (1_1); also elsewhere on the board
/Blinking: K2.3; also elsewhere on the board
/Continous: K2.4; also elsewhere on the board
/Red: K1.3; also elsewhere on the board
/SR: Q13.1 (G), TP6.1 (1_1); also elsewhere on the board
GND: Q13.2 (S), Q14.2 (S); also elsewhere on the board
unnamed: D30.2 (A), K1.5, Q13.3 (D)
unnamed: D31.2 (A), K2.5, Q14.3 (D)
unnamed: K1.1, K1.6, K2.1, K2.6

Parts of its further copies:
D32, D33, D34, D35: M7; D_SMA
K3, K4, K5, K6: HRB1-S-DC12V; RELAY-TH_HRB1-S-X; MPN HRB1-S-DC12V; LCSC Part C125705
Q15, Q16, Q17, Q18: 2N7002W; SOT-323_SC-70; MPN 2N7002W; LCSC Part C7420322
TP8, TP10: SEL; TestPoint_Pad_D1.0mm
TP9, TP11: BLNK; TestPoint_Pad_D1.0mm

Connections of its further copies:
+12V: D32.1 (K), D33.1 (K), D34.1 (K), D35.1 (K), K3.2, K4.2, K5.2, K6.2; also elsewhere on the board
/BG: Q18.1 (G), TP11.1 (1_1); also elsewhere on the board
/BY: Q16.1 (G), TP9.1 (1_1); also elsewhere on the board
/Blinking: K4.3, K6.3; also elsewhere on the board
/Continous: K4.4, K6.4; also elsewhere on the board
/Green: K5.3; also elsewhere on the board
/SG: Q17.1 (G), TP10.1 (1_1); also elsewhere on the board
/SY: Q15.1 (G), TP8.1 (1_1); also elsewhere on the board
/Yellow: K3.3; also elsewhere on the board
GND: Q15.2 (S), Q16.2 (S), Q17.2 (S), Q18.2 (S); also elsewhere on the board
unnamed: D32.2 (A), K3.5, Q15.3 (D)
unnamed: D33.2 (A), K4.5, Q16.3 (D)
unnamed: D34.2 (A), K5.5, Q17.3 (D)
unnamed: D35.2 (A), K6.5, Q18.3 (D)
unnamed: K3.1, K3.6, K4.1, K4.6
unnamed: K5.1, K5.6, K6.1, K6.6

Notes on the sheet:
150mW 12V 12.5mA
Max Power: 2x Relay = 300mW 25mA Power Dissipation per MOSFET: max PD = R_{DS(on)} * (12.5mA)^{2} = @{format(2 * 0.0125^2 * 1000, 3)}mW @ R_{DS(on)}=2Ω
Both Sink connections/wires (Continous and Blinking) are internally protected against reverse currentflow and therefor dont impose a risk of short circuits when connected together. The Continously on Sink overrules the Blinking Sink in the case that both are connected to an LED at the same time. St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
